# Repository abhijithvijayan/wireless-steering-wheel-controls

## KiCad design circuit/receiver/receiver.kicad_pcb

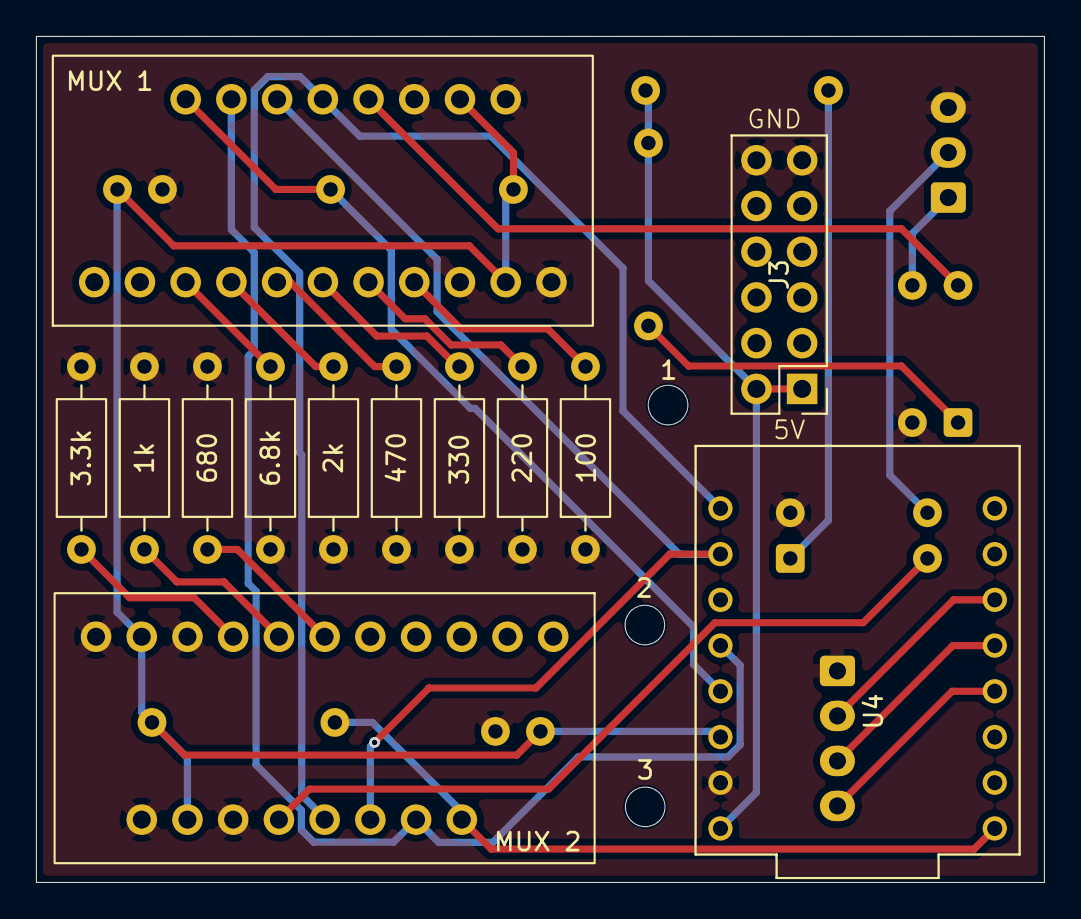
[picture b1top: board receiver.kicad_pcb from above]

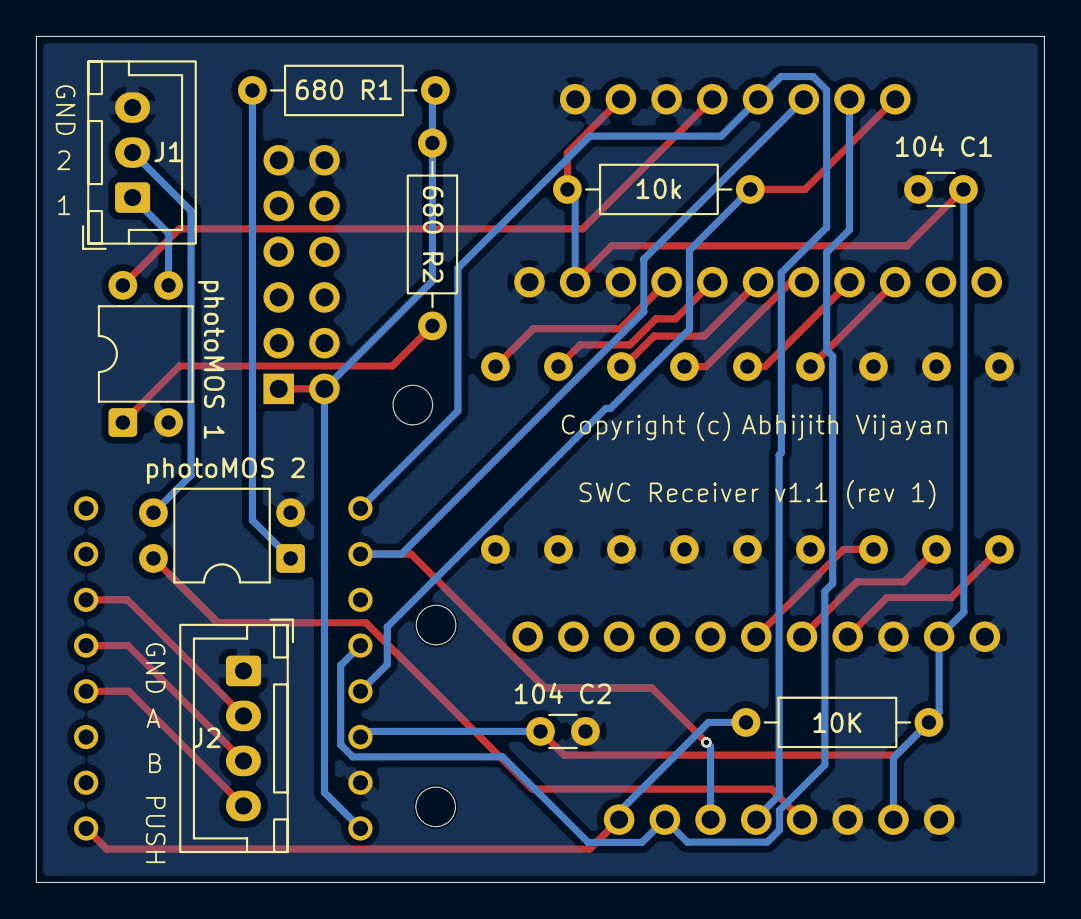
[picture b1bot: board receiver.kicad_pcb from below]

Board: 2 copper layers, 56.0 x 47.0 mm, 26 parts (10 on the bottom side), 26 nets.

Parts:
1, 2, 3: MountingHole_2.2mm_M2
1k: 1k; R_Axial_DIN0207_L6.3mm_D2.5mm_P10.16mm_Horizontal
2k: 2k; R_Axial_DIN0207_L6.3mm_D2.5mm_P10.16mm_Horizontal
3.3k: 3.3k; R_Axial_DIN0207_L6.3mm_D2.5mm_P10.16mm_Horizontal
6.8k: 6.8k; R_Axial_DIN0207_L6.3mm_D2.5mm_P10.16mm_Horizontal
10K, 10k: 10k; R_Axial_DIN0207_L6.3mm_D2.5mm_P10.16mm_Horizontal
100: 100; R_Axial_DIN0207_L6.3mm_D2.5mm_P10.16mm_Horizontal
104 C1, 104 C2: 100nF; C_Disc_D3.0mm_W1.6mm_P2.50mm
220: 220; R_Axial_DIN0207_L6.3mm_D2.5mm_P10.16mm_Horizontal
330: 330; R_Axial_DIN0207_L6.3mm_D2.5mm_P10.16mm_Horizontal
470: 470; R_Axial_DIN0207_L6.3mm_D2.5mm_P10.16mm_Horizontal
680, 680 R1, 680 R2: 680; R_Axial_DIN0207_L6.3mm_D2.5mm_P10.16mm_Horizontal
J1: Conn_01x03_Pin; JST_XH_B3B-XH-A_1x03_P2.50mm_Vertical
J2: Conn_01x04_Pin; JST_XH_B4B-XH-A_1x04_P2.50mm_Vertical
J3: Conn_02x06_Top_Bottom; PinHeader_2x06_P2.54mm_Vertical
MUX 1, MUX 2: 74HC4051; MUX_74HC4051_Module
U4: ESP32-C3_SUPERMINI_TH; MODULE_ESP32-C3_SUPERMINI_TH
photoMOS 1, photoMOS 2: AQY212EH; DIP-4_W7.62mm

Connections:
GND: 1k.2, 2k.1, 3.3k.2, 6.8k.1, 100.1, 104 C1.1, 104 C2.2, 220.1, 330.1, 470.1, 680.2, J1.3, J2.1, J3.11, J3.12, MUX 1.7 (VEE), MUX 1.8 (GND), MUX 2.7 (VEE), MUX 2.8 (GND), U4.G (GND), photoMOS 1.2, photoMOS 2.2
unnamed: J1.1, photoMOS 1.3
unnamed: J1.2, photoMOS 2.3
unnamed: J2.2, U4.10 (GPIO10)
unnamed: J2.3, U4.9 (GPIO9)
unnamed: J2.4, U4.8 (GPIO8)
unnamed: 680 R1.1, 680 R2.1, J3.1, J3.2, U4.5V
unnamed: 680 R2.2, photoMOS 1.1
unnamed: 680 R1.2, photoMOS 2.1
unnamed: 3.3k.1, MUX 2.13 (A0)
unnamed: 1k.1, MUX 2.14 (A1)
unnamed: 680.1, MUX 2.15 (A2)
unnamed: MUX 2.3 (A), photoMOS 2.4
unnamed: MUX 1.11 (S0), MUX 2.11 (S0), U4.0 (GPIO0)
unnamed: MUX 1.10 (S1), MUX 2.10 (S1), U4.1 (GPIO1)
unnamed: MUX 1.9 (S2), MUX 2.9 (S2), U4.3 (GPIO3)
unnamed: 10K.2, 10k.1, 104 C1.2, 104 C2.1, MUX 1.16 (VCC), MUX 2.16 (VCC), U4.3.3 (3V3)
unnamed: 10K.1, MUX 2.6 (~E), U4.5 (GPIO5)
unnamed: 100.2, MUX 1.13 (A0)
unnamed: 220.2, MUX 1.14 (A1)
unnamed: 330.2, MUX 1.15 (A2)
unnamed: 470.2, MUX 1.12 (A3)
unnamed: 2k.2, MUX 1.1 (A4)
unnamed: 6.8k.2, MUX 1.5 (A5)
unnamed: MUX 1.3 (A), photoMOS 1.4
unnamed: 10k.2, MUX 1.6 (~E), U4.4 (GPIO4)

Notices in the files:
circuit/receiver/receiver.kicad_pcb:
Copyright (c) Abhijith Vijayan
